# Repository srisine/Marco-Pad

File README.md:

# Marco-Pad

<h1>A Macro Pad inspired by Marco Polo!</h1>

my first attempt at pcb and cad designing 

Not the most perfect pcb but still i managed to build smtn in KiCAD
<h1>PCB:</h1>

Then i build an enclosure in Fusion 360 (First time ever)

<h1>CAD</h1>

<h2>V1</h2>

<h2>V2</h2>

<h2>V3(Added screw threads)</h2>

<h1>Firmware overview</h1>
Then i used QMK to write a firmware

Rotary Encoder: for volume and mute/unmute
4 Buttons: for media control 
Oled: for status indicator

### 📦 Bill of Materials (BOM)

| Component | Quantity | Description |
| :--- | :---: | :--- |
| MX-Style Switches | 4x | Mechanical switches for the main keys |
| DSA Keycaps | 4x | White blank DSA profile keycaps |
| EC11 Rotary Encoder | 1x | Rotary encoder with integrated push switch |
| OLED Display | 1x | 0.91-inch I2C OLED display |
| M3 Screws | 4x | M3 x 16mm screws for the sandwich case |
| Microcontroller | 1x | Seeed Studio XIAO RP2040 (unsoldered) |
| Case | 1x | Custom 3D printed sandwich case (2 parts) |

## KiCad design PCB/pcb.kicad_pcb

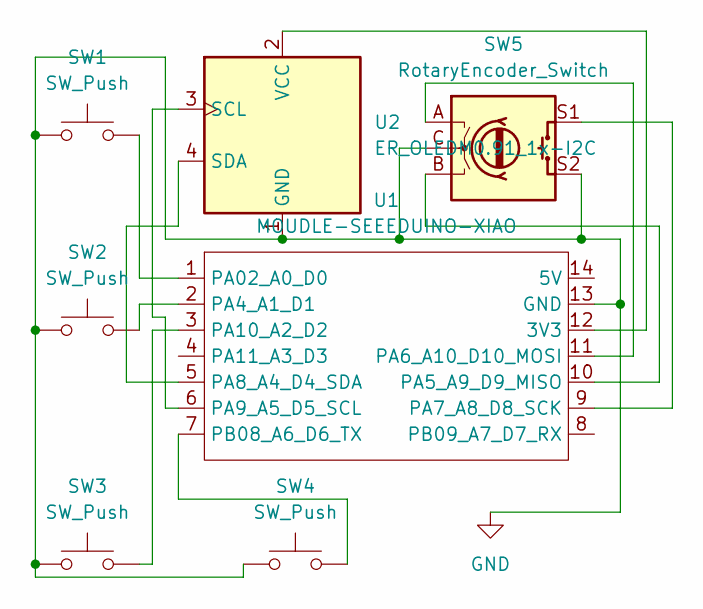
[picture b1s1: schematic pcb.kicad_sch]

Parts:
SW1, SW2, SW3, SW4: SW_Push; SW_Cherry_MX_1.00u_PCB
SW5: RotaryEncoder_Switch; RotaryEncoder_Alps_EC11E-Switch_Vertical_H20mm
U1: MOUDLE-SEEEDUINO-XIAO; XIAO-Generic-Hybrid-14P-2.54-21X17.8MM
U2: ER_OLEDM0.91_1x-I2C

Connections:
GND: SW1.1, SW2.1, SW3.1, SW4.1, SW5.C, SW5.S2, U1.13 (GND), U2.1 (GND)
unnamed: U1.12 (3V3), U2.2 (VCC)
unnamed: SW1.2, U1.1 (PA02_A0_D0)
unnamed: SW2.2, U1.2 (PA4_A1_D1)
unnamed: SW5.B, U1.10 (PA5_A9_D9_MISO)
unnamed: SW5.A, U1.11 (PA6_A10_D10_MOSI)
unnamed: SW5.S1, U1.9 (PA7_A8_D8_SCK)
unnamed: U1.5 (PA8_A4_D4_SDA), U2.4 (SDA)
unnamed: U1.6 (PA9_A5_D5_SCL), U2.3 (SCL)
unnamed: SW3.2, U1.3 (PA10_A2_D2)
unnamed: SW4.2, U1.7 (PB08_A6_D6_TX)

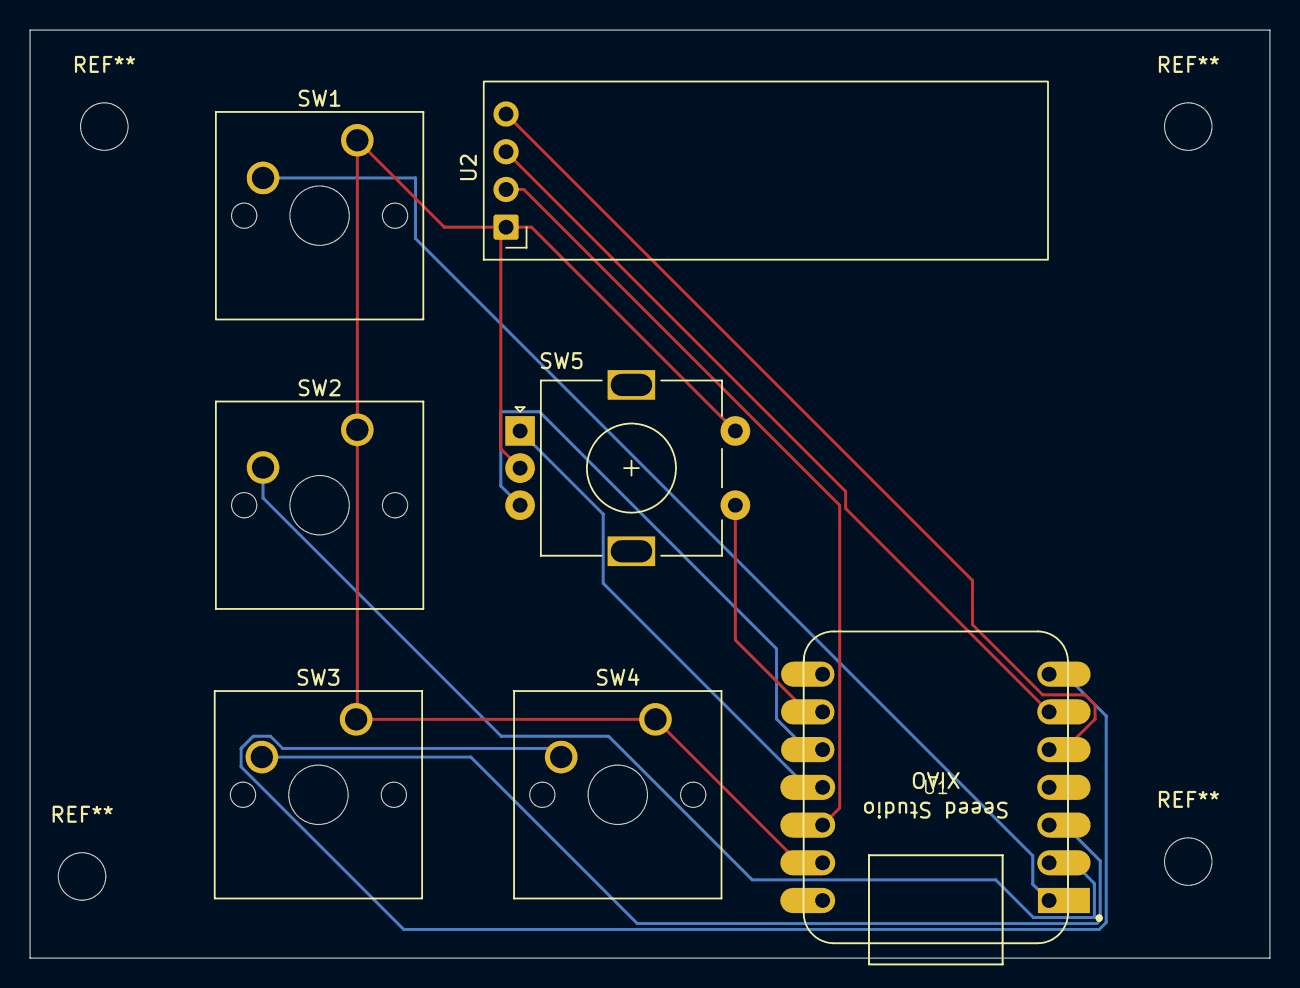
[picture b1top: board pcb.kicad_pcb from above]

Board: 2 copper layers, 83.5 x 62.5 mm, 7 parts (0 on the bottom side), 11 nets.
